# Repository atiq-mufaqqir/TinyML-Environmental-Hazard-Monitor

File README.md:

# TinyML-Based Indoor Environmental Monitoring System

## Overview

This project develops a low-cost embedded indoor environmental monitoring system using **multi-sensor fusion and TinyML-based classification**.

The system uses an **STM32 Nucleo-L476RG microcontroller** to collect environmental data from multiple sensors, process the data locally, and classify indoor conditions in real time.

Unlike traditional threshold-based air-quality monitoring systems, this project uses machine learning to identify patterns across multiple environmental parameters and classify different indoor events:

- Normal background conditions
- Cooking activity
- Aerosol spray usage

The trained TinyML model is deployed directly onto the STM32 microcontroller, enabling real-time edge inference without cloud processing.

---

# Key Features

- Real-time environmental monitoring
- Multi-sensor data fusion
- STM32 embedded firmware development
- TinyML neural network deployment
- Local machine learning inference
- UART-based live monitoring
- Dataset collection and processing
- Custom PCB design using KiCad

---

# System Architecture

# Hardware Components

## STM32 Nucleo-L476RG

The STM32 Nucleo-L476RG was selected as the embedded processing platform.

Features used:

- ARM Cortex-M4 processor
- STM32CubeIDE development environment
- STM32 HAL libraries
- I2C communication
- UART communication
- Embedded TinyML inference

---

# Environmental Sensors

## Bosch BME688

Measurements:

- Temperature
- Humidity
- Pressure
- Gas resistance

Purpose:

- Detect environmental and gas-related changes caused by indoor activities.

---

## Sensirion SCD41

Measurement:

- Carbon dioxide (CO₂)

Purpose:

- Provides ventilation and occupancy-related information.

---

## Sensirion SPS30

Measurements:

- PM1.0
- PM2.5
- PM4.0
- PM10
- Particle number concentration

Purpose:

- Detects particulate changes caused by cooking and aerosol events.

---

# Hardware Communication

| Component | Interface | STM32 Connection |
|---|---|---|
| BME688 | I2C | PB8/PB9 |
| SCD41 | I2C | PB8/PB9 |
| SPS30 | I2C | PB8/PB9 |
| PC Logging | UART | USART2 |

Communication settings:

```
I2C Speed: 100 kHz
UART Baud Rate: 115200
Sampling Interval: 5 seconds
```

---

# Firmware Development

The firmware was developed using:

- STM32CubeIDE
- STM32CubeMX
- STM32 HAL Drivers

## Firmware Workflow

1. Initialise STM32 peripherals
2. Configure I2C and UART communication
3. Detect connected sensors
4. Initialise sensor drivers
5. Read sensor measurements
6. Format sensor data
7. Output data through UART
8. Run TinyML classification

---

# Dataset Collection

A custom dataset was collected in a domestic kitchen environment.

The system was trained to classify three indoor conditions:

| Class | Description |
|---|---|
| Normal | Background indoor conditions |
| Cooking | Frying activity using an induction hob |
| Aerosol | Deodorant and air freshener spray |

## Dataset Summary

| Class | Number of Readings | Duration |
|---|---|---|
| Normal | 5267 | ~439 minutes |
| Cooking | 879 | ~73 minutes |
| Aerosol | 352 | ~29 minutes |

Sampling interval:

```
One reading every 5 seconds
```

---

# TinyML Model Development

The machine learning model was developed using **Edge Impulse**.

## Model Configuration

Input:

- 15 sensor features
- 60 second time windows
- 180 input features

Neural network:

```
Input Layer
      |
Dense Layer (20 neurons)
      |
Dense Layer (10 neurons)
      |
Output Layer (3 classes)
```

Classes:

```
0 - Aerosol
1 - Cooking
2 - Normal
```

---

# Model Performance

## Training Results

| Metric | Result |
|---|---|
| Training Accuracy | 99.06% |
| Validation Accuracy | 100% |
| Validation Loss | 0.0202 |

---

# Embedded Deployment

The trained model was exported as an embedded C/C++ library and deployed onto the STM32 microcontroller.

Deployment results:

| Resource | Usage |
|---|---|
| Model Type | int8 Quantised Neural Network |
| RAM Usage | 1.6 KB |
| Flash Usage | 17.8 KB |
| Estimated Latency | 1 ms |

---

# Real-Time Classification

The final STM32 prototype successfully performed live classification.

Example output:

```
CO2: 650 ppm
PM2.5: 14 ug/m3
Gas Resistance: 42000 Ohm

Prediction:
NORMAL

Confidence:
96%
```

Testing results:

| Condition | Result |
|---|---|
| Normal Room | Correct |
| Cooking | Correct |
| Aerosol Spray | Correct |

---

# PCB Design

A custom PCB was designed using **KiCad** to improve hardware integration.

Design process:

- Schematic capture
- Component selection
- PCB layout
- Routing
- Electrical Rule Check (ERC)
- Design Rule Check (DRC)

PCB features:

- STM32 interface
- Sensor connectors
- 3.3V and 5V power distribution
- Modular sensor connections

---

# Repository Structure

```
│
├── Core/
│ ├── Inc/
│ └── Src/
│ └── STM32 application firmware
│
├── Drivers/
│ └── STM32 HAL libraries and sensor drivers
│
├── Release/
│ └── Compiled firmware build files
│
├── docs/
│ └── Project documentation and images
│
├── media/
│ └── Project demonstration images/videos
│
├── ml/
│ ├── Dataset/
│ ├── Edge_Impulse/
│ └── Model training files
│
├── pcb/
│ └── KiCad schematic and PCB design files
│
├── TEST.ioc
│ └── STM32CubeMX configuration file
│
├── .project
├── .cproject
│
├── STM32L476RGTX_FLASH.ld
├── STM32L476RGTX_RAM.ld
│
└── README.md
```

---

# Technologies Used

## Embedded Systems

- STM32 Nucleo-L476RG
- ARM Cortex-M4
- STM32CubeIDE
- STM32 HAL
- I2C
- UART

## Sensors

- Bosch BME688
- Sensirion SCD41
- Sensirion SPS30

## Machine Learning

- TinyML
- Edge Impulse
- Neural Networks
- int8 Quantisation

## Hardware Design

- KiCad
- PCB Design
- Embedded Hardware Integration

---

# Limitations

Current limitations:

- Dataset collected from one indoor environment
- Limited aerosol training samples
- Sensor behaviour may vary between locations
- Not a certified air-quality or safety monitoring device
- PCB designed but not manufactured

---

# Future Improvements

Potential improvements:

- Collect larger datasets from different environments
- Add more indoor activity classes
- Add wireless connectivity (BLE/Wi-Fi)
- Develop mobile monitoring application
- Create battery-powered version
- Manufacture and test the PCB
- Compare against traditional threshold systems

---

# Project Outcome

This project demonstrates the use of **TinyML for intelligent embedded environmental monitoring** by combining:

- Sensor fusion
- Embedded firmware
- Machine learning
- Edge inference
- Hardware design

The final prototype successfully collected environmental data, trained a classification model, deployed the model onto an STM32 microcontroller, and performed real-time indoor condition classification.

---

# Author

Atiq Mufaqqir

## License

This project is intended for educational purposes as part of the ELEC3875 Individual Engineering Project.

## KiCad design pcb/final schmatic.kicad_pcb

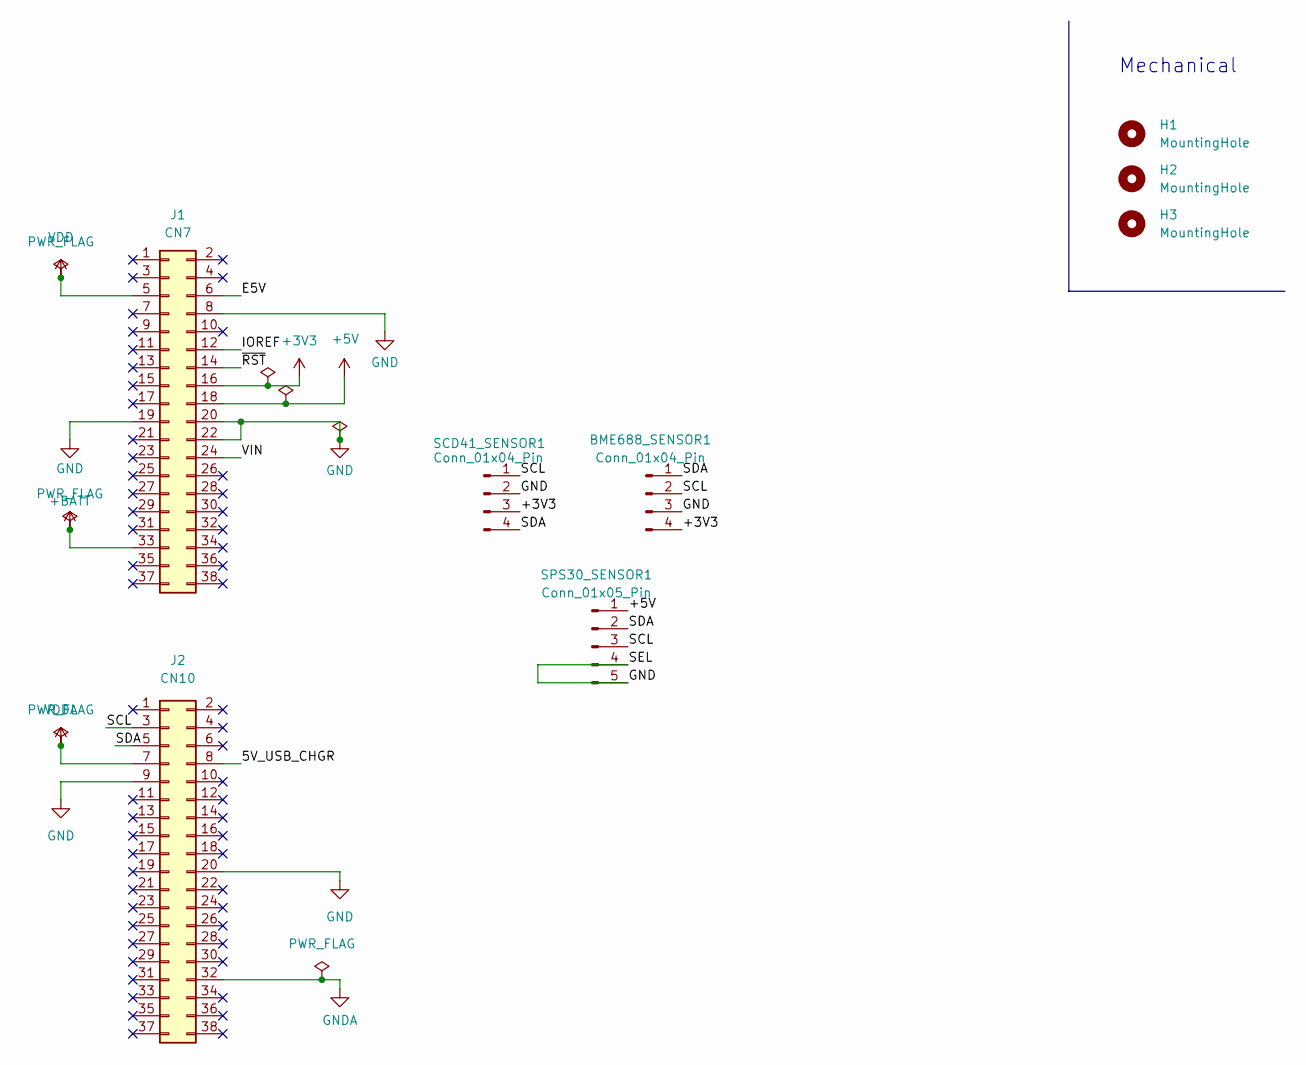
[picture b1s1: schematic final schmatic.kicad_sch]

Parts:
BME688_SENSOR1: Conn_01x04_Pin; PinHeader_1x04_P2.54mm_Vertical
H1, H2, H3: MountingHole; MountingHole_3.2mm_M3
J1: CN7; PinSocket_2x19_P2.54mm_Vertical
J2: CN10; PinSocket_2x19_P2.54mm_Vertical
SCD41_SENSOR1: Conn_01x04_Pin; PinHeader_1x04_P2.54mm_Vertical
SPS30_SENSOR1: Conn_01x05_Pin; PinHeader_1x05_P2.54mm_Vertical

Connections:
+3V3: BME688_SENSOR1.4, J1.16, SCD41_SENSOR1.3
+5V: J1.18, SPS30_SENSOR1.1
+BATT: J1.33
/5V_USB_CHGR: J2.8
/E5V: J1.6
/IOREF: J1.12
/SCL: BME688_SENSOR1.2, J2.3, SCD41_SENSOR1.1, SPS30_SENSOR1.3
/SDA: BME688_SENSOR1.1, J2.5, SCD41_SENSOR1.4, SPS30_SENSOR1.2
/VIN: J1.24
/~RST: J1.14
GND: BME688_SENSOR1.3, J1.8, J1.19, J1.20, J1.22, J2.9, J2.20, SCD41_SENSOR1.2, SPS30_SENSOR1.4, SPS30_SENSOR1.5
GNDA: J2.32
VDD: J1.5
VDDA: J2.7

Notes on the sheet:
Mechanical

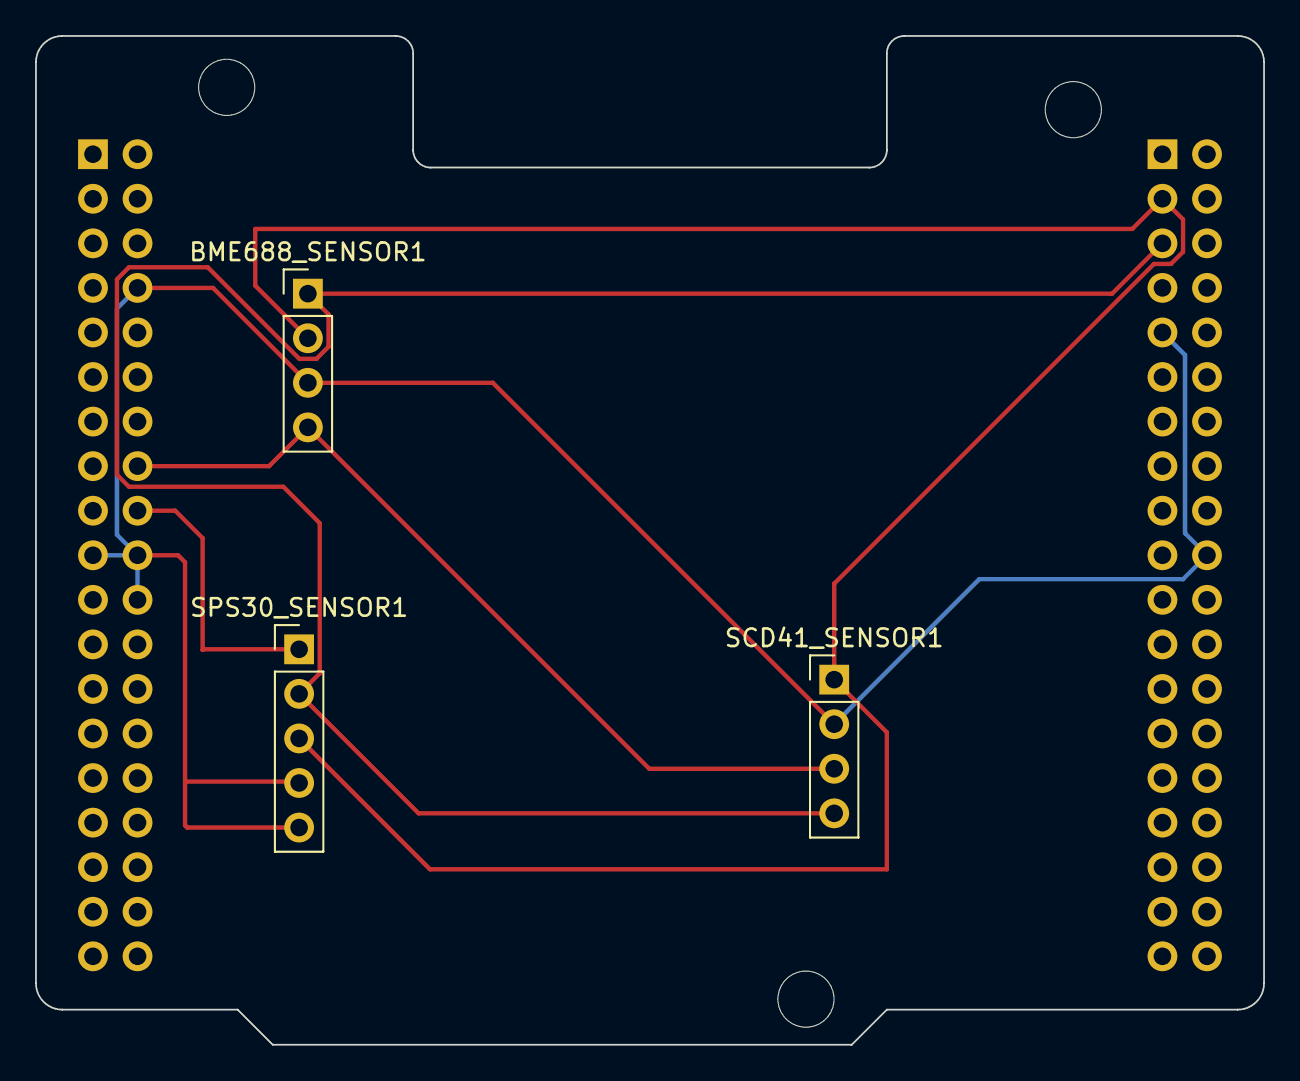
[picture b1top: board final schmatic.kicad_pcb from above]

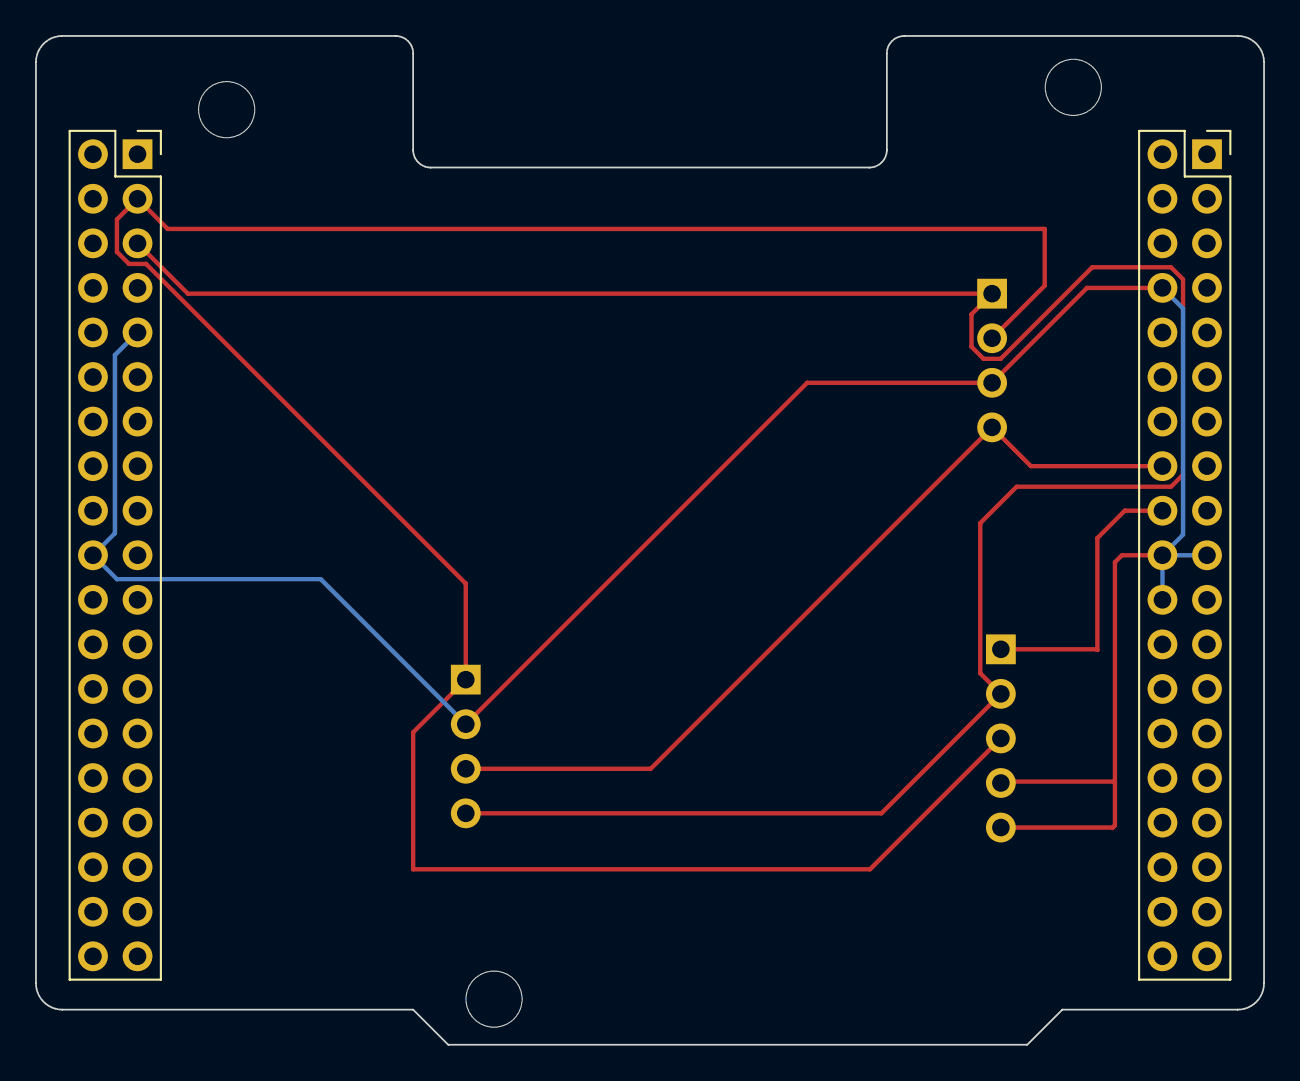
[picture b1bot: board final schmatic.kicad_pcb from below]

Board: 2 copper layers, 70.0 x 57.5 mm, 8 parts (2 on the bottom side), 5 nets.
